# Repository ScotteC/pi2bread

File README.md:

## pi2bread

Just a simple connector board to distribute a Raspberry Pis GPIO port to your breadboard.

Another one? Why? Why not unsing an existing one???
Because i don't like the existing ones.
Most of the avaliable connectors distribute the pins as exact copy of the original GPIO header, including the supply pins.
This version separates signal and supply pins, add jumpers to cut the supplys and rearranges the pinuout, based on some personal needs.

## Licence

    Copyright Fabian Schöttler 2021.

    This source describes Open Hardware and is licensed under the CERN-OHL-S v2.

    You may redistribute and modify this source and make products using it under
    the terms of the CERN-OHL-S v2 ( https://ohwr.org/cernohlsv2.txt ).

    This  source  is  distributed  WITHOUT  ANY  EXPRESS  OR  IMPLIEDWARRANTY, 
    INCLUDING OF MERCHANTABILITY, SATISFACTORYQUALITY AND FITNESS FOR A PARTICULAR PURPOSE. 
    Please see the CERN-OHL-S v2 for applicable conditions.

    Source location:  https://github.com/ScotteC/pi2bread

    As per CERN-OHL-S v2 section 4, should You produce hardware based on this source, 
    You must where practicable maintain the Source Location visible on the external 
    case of the pi2bread or other products you make using this source.

You can find the full license text in the [LICENCE](LICENCE) file.

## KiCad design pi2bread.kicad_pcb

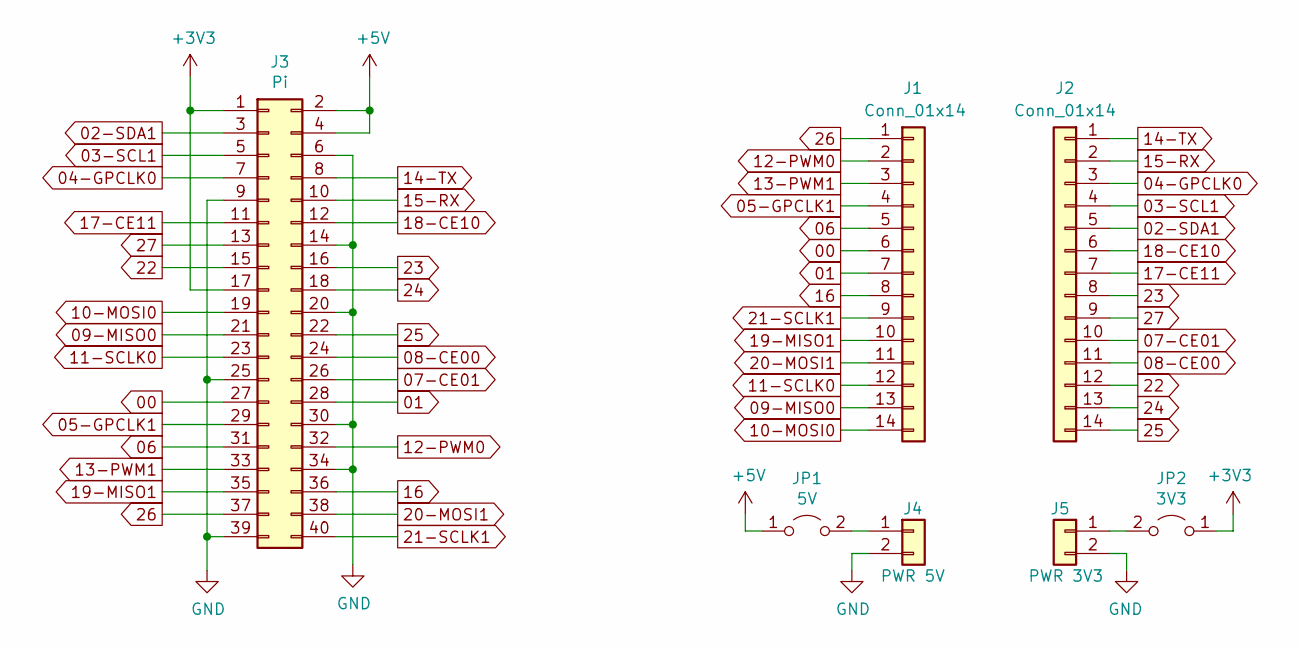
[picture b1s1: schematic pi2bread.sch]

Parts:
J1, J2: Conn_01x14; PinHeader_1x14_P2.54mm_Vertical
J3: Pi; vasch_strip_20x2
J4: PWR 5V; PinHeader_1x02_P2.54mm_Vertical
J5: PWR 3V3; PinHeader_1x02_P2.54mm_Vertical
JP1: 5V; PinHeader_1x02_P2.54mm_Vertical
JP2: 3V3; PinHeader_1x02_P2.54mm_Vertical

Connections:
00: J1.6, J3.27
01: J1.7, J3.28
02-SDA1: J2.5, J3.3
03-SCL1: J2.4, J3.5
04-GPCLK0: J2.3, J3.7
05-GPCLK1: J1.4, J3.29
06: J1.5, J3.31
07-CE01: J2.10, J3.26
08-CE00: J2.11, J3.24
09-MISO0: J1.13, J3.21
10-MOSI0: J1.14, J3.19
11-SCLK0: J1.12, J3.23
12-PWM0: J1.2, J3.32
13-PWM1: J1.3, J3.33
14-TX: J2.1, J3.8
15-RX: J2.2, J3.10
16: J1.8, J3.36
17-CE11: J2.7, J3.11
18-CE10: J2.6, J3.12
19-MISO1: J1.10, J3.35
20-MOSI1: J1.11, J3.38
21-SCLK1: J1.9, J3.40
22: J2.12, J3.15
23: J2.8, J3.16
24: J2.13, J3.18
25: J2.14, J3.22
26: J1.1, J3.37
27: J2.9, J3.13
+3V3: J3.1, J3.17, JP2.1 (A)
+5V: J3.2, J3.4, JP1.1 (A)
GND: J3.6, J3.9, J3.14, J3.20, J3.25, J3.30, J3.34, J3.39, J4.2, J5.2
unnamed: J4.1, JP1.2 (B)
unnamed: J5.1, JP2.2 (B)

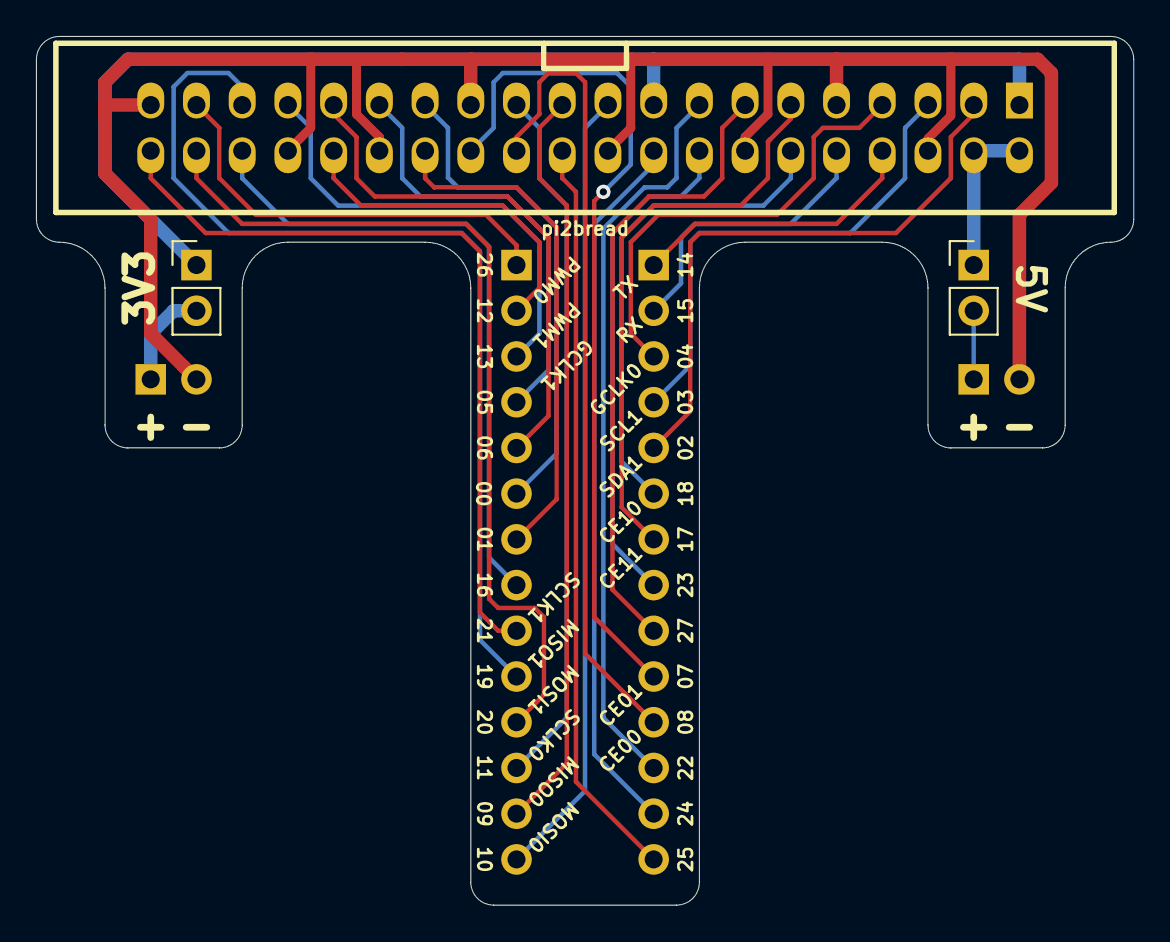
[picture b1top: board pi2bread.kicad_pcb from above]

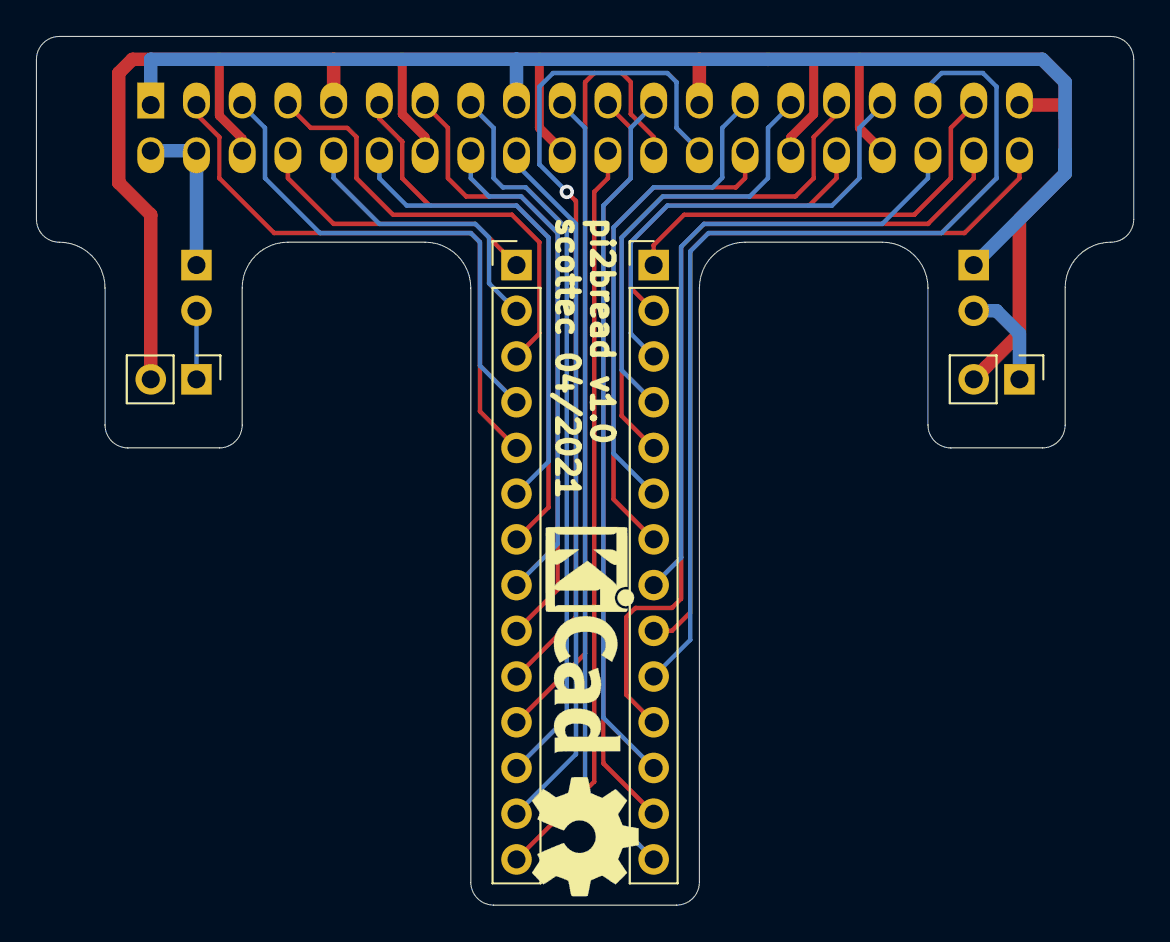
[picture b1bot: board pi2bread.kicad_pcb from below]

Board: 2 copper layers, 61.0 x 48.3 mm, 7 parts (4 on the bottom side), 33 nets.

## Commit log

2021-04-20 add licence
2021-04-21 add file informations
